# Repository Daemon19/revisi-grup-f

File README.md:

# 🤖 Revisi Grup F Bayucaraka

Repositori ini berisi hasil pengembangan dan revisi **Final Project Bayucaraka**, yang mencakup tiga bagian utama:

- ⚡ **Electrical**: desain PCB, skematik, dan firmware mikrokontroler.
- 🔧 **Mechanical**: model CAD komponen dan assembly.
- 💻 **Programming**: workspace pemrograman tambahan (MCU/ROS/script).

## 📝 Catatan

- Catatan revisi yang dilakukan dapat ditemukan pada README di masing-masing directory subdivisi
- Folder `Demo` menyimpan versi saat demo.
- Folder `Revisi` adalah hasil perbaikan akhir.

## 🎯 Tujuan Proyek

Proyek ini membangun sistem aktuator berbasis **ESP32** untuk mekanisme pemindahan objek (pick-and-place sederhana), dengan kombinasi:

- 🔀 2 sumbu gerak linear menggunakan motor stepper (X dan Y),
- 🎮 2 servo untuk mekanisme capit dan naik-turun,
- 🏠 limit switch sebagai referensi gerak/home.

## 📁 Struktur Folder Utama

- ⚡ `electrical/`
  - `Demo/`: versi awal desain dan kode.
  - `Revisi/`: versi perbaikan (PCB + firmware final revisi).
    - `CNC V4 Power Jack (PCB)/`: file KiCad (`.kicad_pcb`, `.kicad_sch`, dsb).
    - `FP BAYUCARAKA/`: proyek PlatformIO firmware ESP32.
- 🔧 `mechanical/`
  - `Demo/`: model mekanik sebelum revisi.
  - `Revisi/`: model mekanik setelah revisi.
- 💻 `programming/`
  - `Demo/`: folder pengembangan kode MCU/ROS/script.
  - `Revisi/`: folder lanjutan untuk revisi pemrograman.

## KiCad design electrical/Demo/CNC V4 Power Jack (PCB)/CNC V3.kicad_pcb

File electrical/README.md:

# ⚡ Revisi Electrical

## 🖨️ PCB

Polaritas kapsitor 100uF pada front.silkscreen terbalik, sehingga dibenarkan di versi revisi

## 💾 KODE

Capit tidak terbuka maksimal sesuai yang dibutuhkan, maka value lebih disesuaikan pada int buka di fungsi `void capit()`.

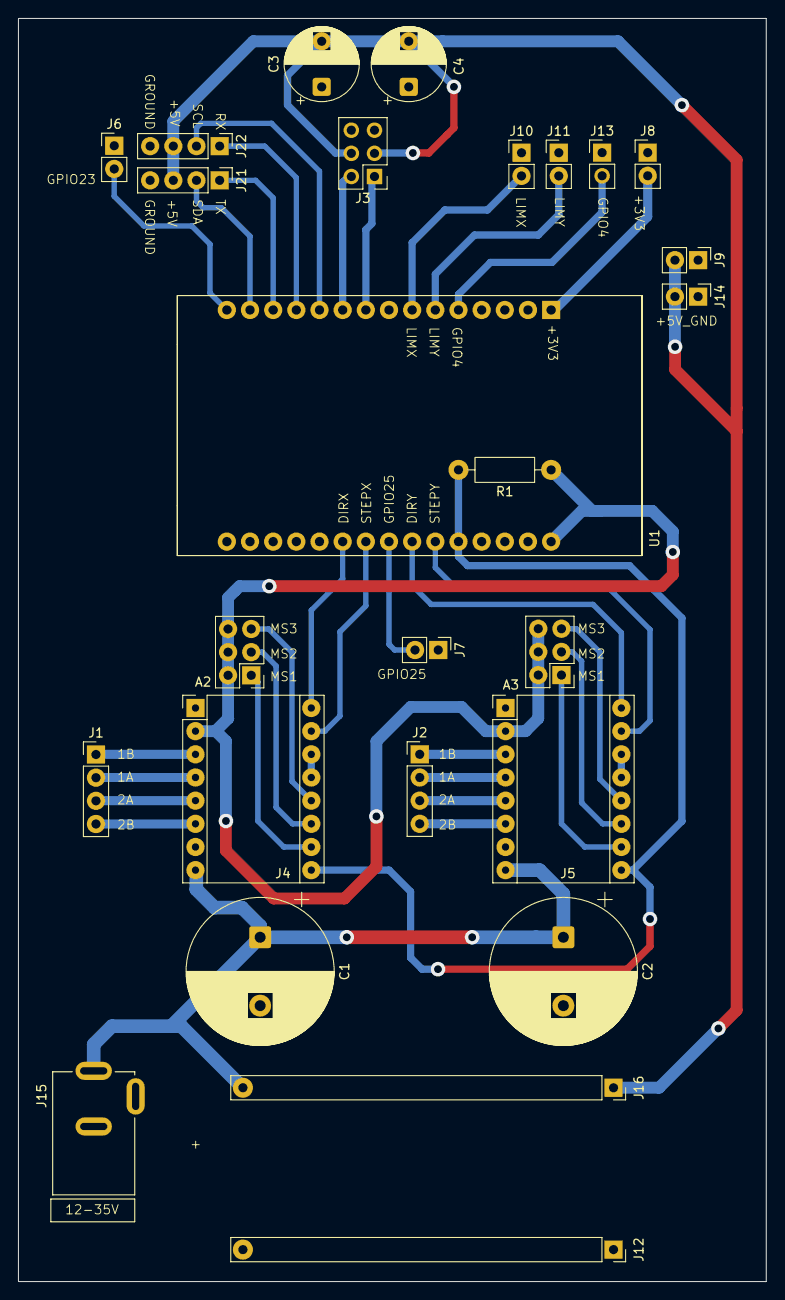
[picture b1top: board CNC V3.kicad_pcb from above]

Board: 2 copper layers, 82.0 x 138.5 mm, 26 parts (0 on the bottom side), 37 nets.

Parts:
A2, A3: Pololu_Breakout_A4988; Pololu_Breakout-16_15.2x20.3mm
C1, C2: 1000uF; CP_Radial_D16.0mm_P7.50mm
C3, C4: 100uF; CP_Radial_D8.0mm_P5.00mm
J1, J2, J21, J22: Conn_01x04; PinHeader_1x04_P2.54mm_Vertical
J3, J4, J5: Conn_02x03_Odd_Even; PinHeader_2x03_P2.54mm_Vertical
J6, J7, J8, J9, J10, J11, J13, J14: Conn_01x02; PinHeader_1x02_P2.54mm_Vertical
J12, J16: Conn_01x17; PinSocket_1x17_P2.54mm_Vertical
J15: CON-SOCJ-2155; GRAVITECH_CON-SOCJ-2155
R1: 10K; R_Axial_DIN0207_L6.3mm_D2.5mm_P10.16mm_Horizontal
U1: ESP32-DEVKIT-V1; MODULE_ESP32_DEVKIT_V1

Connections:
+3V3: J8.2, U1.1 (3V3)
+5V: A2.2 (VDD), A3.2 (VDD), J4.2, J4.4, J4.6, J5.2, J5.4, J5.6, R1.1, U1.30 (VIN)
+EX5V: C3.2, C4.2, J3.3, J3.4, J9.2, J14.2, J16.1, J21.3, J22.3
DIRX: A2.16 (DIR), U1.21 (D32)
DIRY: A3.16 (DIR), U1.24 (D26)
EN: A2.9 (~ENABLE), A3.9 (~ENABLE), R1.2, U1.26 (D14)
EXT_V: A2.8 (VMOT), A3.8 (VMOT), C1.1, C2.1, J15.1, J16.17
GND: A2.1 (GND), A2.7 (GND), A3.1 (GND), A3.7 (GND), C1.2, C2.2, C3.1, C4.1, J3.5, J3.6, J6.1, J7.1, J8.1, J9.1, J10.1, J11.1, J12.1, J12.17, J13.1, J14.1, J15.2, J15.3, J21.4, J22.4, U1.2 (GND), U1.29 (GND)
GPIO4: J13.2, U1.5 (D4)
GPIO23: J6.2, U1.15 (D23)
GPIO25: J7.2, U1.23 (D25)
LIMX: J10.2, U1.7 (TX2)
LIMY: J11.2, U1.6 (RX2)
unnamed: A2.4 (1A), J1.2
unnamed: A2.3 (1B), J1.1
unnamed: A2.5 (2A), J1.3
unnamed: A2.6 (2B), J1.4
unnamed: A2.10 (MS1), J4.1
unnamed: A2.11 (MS2), J4.3
unnamed: A2.12 (MS3), J4.5
unnamed: A2.13 (~RESET), A2.14 (~SLEEP)
unnamed: A3.4 (1A), J2.2
unnamed: A3.3 (1B), J2.1
unnamed: A3.5 (2A), J2.3
unnamed: A3.6 (2B), J2.4
unnamed: A3.10 (MS1), J5.1
unnamed: A3.11 (MS2), J5.3
unnamed: A3.12 (MS3), J5.5
unnamed: A3.13 (~RESET), A3.14 (~SLEEP)
RX: J22.1, U1.12 (RX0)
SCL: J22.2, U1.11 (D21)
SDA: J21.2, U1.14 (D22)
SERVO_CAPIT: J3.1, U1.9 (D18)
SERVO_NT: J3.2, U1.10 (D19)
STEPX: A2.15 (STEP), U1.22 (D33)
STEPY: A3.15 (STEP), U1.25 (D27)
TX: J21.1, U1.13 (TX0)

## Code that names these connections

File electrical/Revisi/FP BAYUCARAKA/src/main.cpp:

#include <Arduino.h>
#include <ESP32Servo.h>

#define SERVO_NT 18
#define SERVO_C 19
#define STEPX 33
#define DIRX 32
#define STEPY 27
#define DIRY 26
#define LIMX 16
#define LIMY 17
#define ENABLE 14

void mission(float x_load, float y_load, float x_drop, float y_drop);
void moveToTarget(float x, float y);
void test();
void home();
void capit(bool arah);
void naikturun(bool arah);

Servo servoc;
Servo servont;

const float stepsPerRevolution = 1600;
const float max_x = 41.4;
const float max_y = 45.4;
const float min_arm_x = 0;
const float min_arm_y = 9;
const float max_arm_y = max_y - 9;
const float max_revolution_x = 7;
const float max_revolution_y = 7.275;
const float stepsPercm_x = (stepsPerRevolution * max_revolution_x) / max_x;
const float stepsPercm_y = (stepsPerRevolution * max_revolution_y) / max_y;
float position_x = 0;
float position_y = 9;

void setup() {
  Serial.begin(115200);
  pinMode(ENABLE, OUTPUT);
  pinMode(STEPX, OUTPUT);
  pinMode(DIRX, OUTPUT);
  pinMode(STEPY, OUTPUT);
  pinMode(DIRY, OUTPUT);
  pinMode(LIMX, INPUT_PULLUP);
  pinMode(LIMY, INPUT_PULLUP);
  pinMode(SERVO_C, OUTPUT);
  pinMode(SERVO_NT, OUTPUT);

  digitalWrite(ENABLE, LOW);

  servoc.attach(SERVO_C);
  servont.attach(SERVO_NT);
  servoc.write(100);
  servont.write(140);
}

void loop() {

}

void mission(float x_load, float y_load, float x_drop, float y_drop){
  moveToTarget(x_load, y_load);
  delay(3000);
  naikturun(true);
  delay(3000);
  capit(true);
  delay(3000);
  naikturun(false);
  delay(3000);
  moveToTarget(x_drop, y_drop);
  delay(3000);
  naikturun(true);
  delay(3000);
  capit(false);
  delay(3000);
  naikturun(false);
  delay(3000);
  moveToTarget(0, 0);
  delay(3000);
}

void moveToTarget(float x, float y) {
  float selisih_X = x - position_x;
  float stepsX = abs(selisih_X) * stepsPercm_x;

  digitalWrite(DIRX, selisih_X > 0 ? HIGH : LOW);
  Serial.printf("stepsX: %f\n", stepsX);

  for (int i = 0; i < stepsX; i++) {
    digitalWrite(STEPX, HIGH);
    delayMicroseconds(500);
    digitalWrite(STEPX, LOW);
    delayMicroseconds(500);
  }

  position_x = x;

  float selisih_Y = y - position_y;
  float stepsY = abs(selisih_Y) * stepsPercm_y;

  digitalWrite(DIRY, selisih_Y > 0 ? LOW : HIGH);
  Serial.printf("stepsY: %f\n", stepsY);

  for (int i = 0; i < stepsY; i++) {
    digitalWrite(STEPY, HIGH);
    delayMicroseconds(500);
    digitalWrite(STEPY, LOW);
    delayMicroseconds(500);
  }

  position_y = y;
}

// void test(){
//   digitalWrite(DIRX, HIGH);
//   int stepsX = 0;

//   while(digitalRead(LIMX) != LOW){
//     digitalWrite(STEPX, HIGH);
//     delayMicroseconds(500);
//     digitalWrite(STEPX, LOW);
//     delayMicroseconds(500);
//     stepsX++;
//     Serial.printf("stepsX: %d\n", stepsX);
//   }
  
//   digitalWrite(DIRY, LOW);
//   int stepsY = 0;

//   while(digitalRead(LIMY) != LOW){
//     digitalWrite(STEPY, HIGH);
//     delayMicroseconds(500);
//     digitalWrite(STEPY, LOW);
//     delayMicroseconds(500);
//     stepsY++;
//     Serial.printf("stepsY: %d\n", stepsY);
//   }
// }

// void home(){
//   digitalWrite(DIRX, LOW);

//   while(digitalRead(LIMX) != LOW){
//     digitalWrite(STEPX, HIGH);
//     delayMicroseconds(500);
//     digitalWrite(STEPX, LOW);
//     delayMicroseconds(500);
//   }
  
//   digitalWrite(DIRY, HIGH);

//   while(digitalRead(LIMY) != LOW){
//     digitalWrite(STEPY, HIGH);
//     delayMicroseconds(500);
//     digitalWrite(STEPY, LOW);
//     delayMicroseconds(500);
//   }

//   position_x = 0;
//   position_y = 0;
// }

void capit(bool arah) {
  int buka = 70;
  int tutup = 100;

  if (arah) {
    for (int i = buka; i <= tutup; i++) {
      servoc.write(i);
      delay(10);
    }
    delay(10);
  } else {
    for (int i = tutup; i >= buka; i--) {
      servoc.write(i);
      delay(10);
    }
    delay(10);
  }
}

void naikturun(bool arah) {
  int naik = 100;
  int turun = 80;

  if (arah) {
    for (int i = turun; i < naik; i++) {
      servont.write(i);
      delay(10);
    }
    delay(10);
  } else {
    for (int b = naik; b > turun; b--) {
      servont.write(b);
      delay(10);
    }
    delay(10);
  }
}

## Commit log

2026-03-05 menambahkan file demo dan revisi
2026-03-05 menghapus .vscode dari electrical
2026-03-05 menambahkan revisi programming
2026-03-05 add readme files
2026-03-05 add emoji to readme
